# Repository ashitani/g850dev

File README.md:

# g850dev

[ポケコンPC-G850V の開発メモ](https://ashitani.jp/g850/)
のサンプルプログラムやツール類などです。

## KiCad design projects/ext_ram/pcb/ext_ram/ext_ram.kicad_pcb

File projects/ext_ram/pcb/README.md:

# pcb design for pc-g850 memory extension board

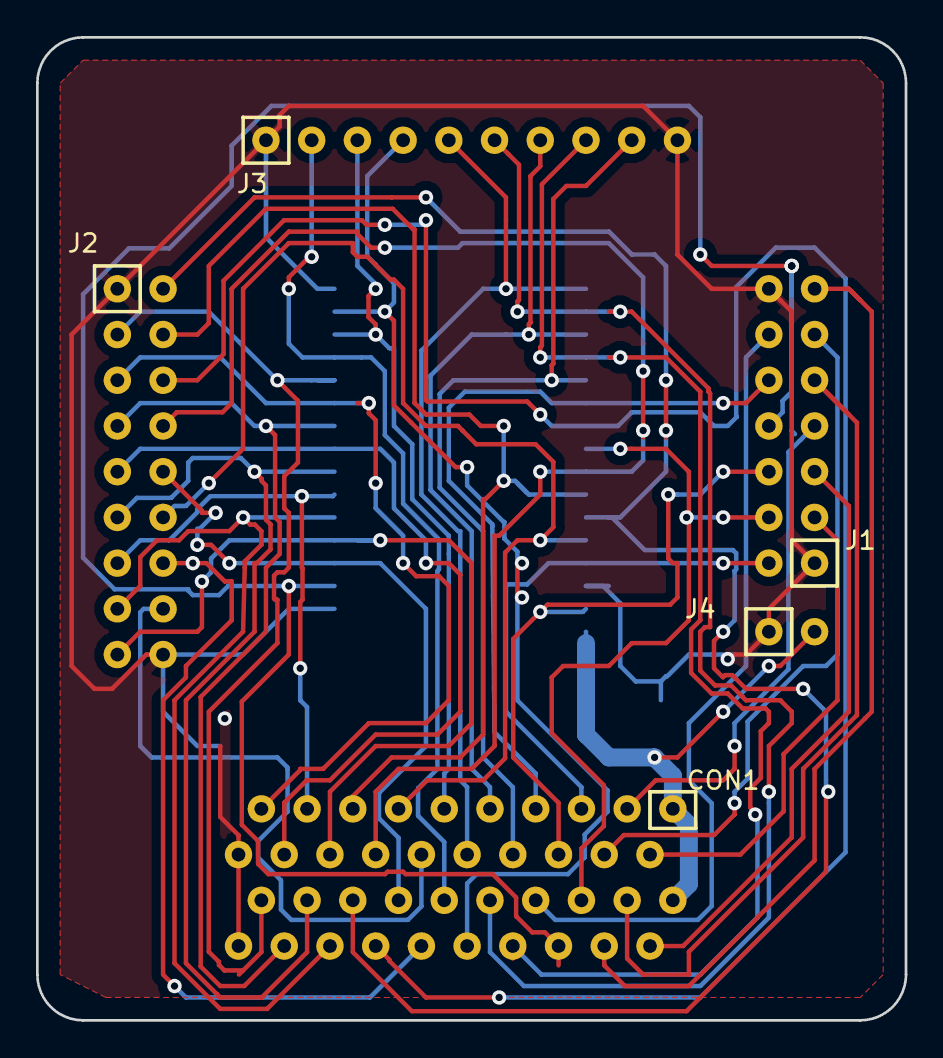
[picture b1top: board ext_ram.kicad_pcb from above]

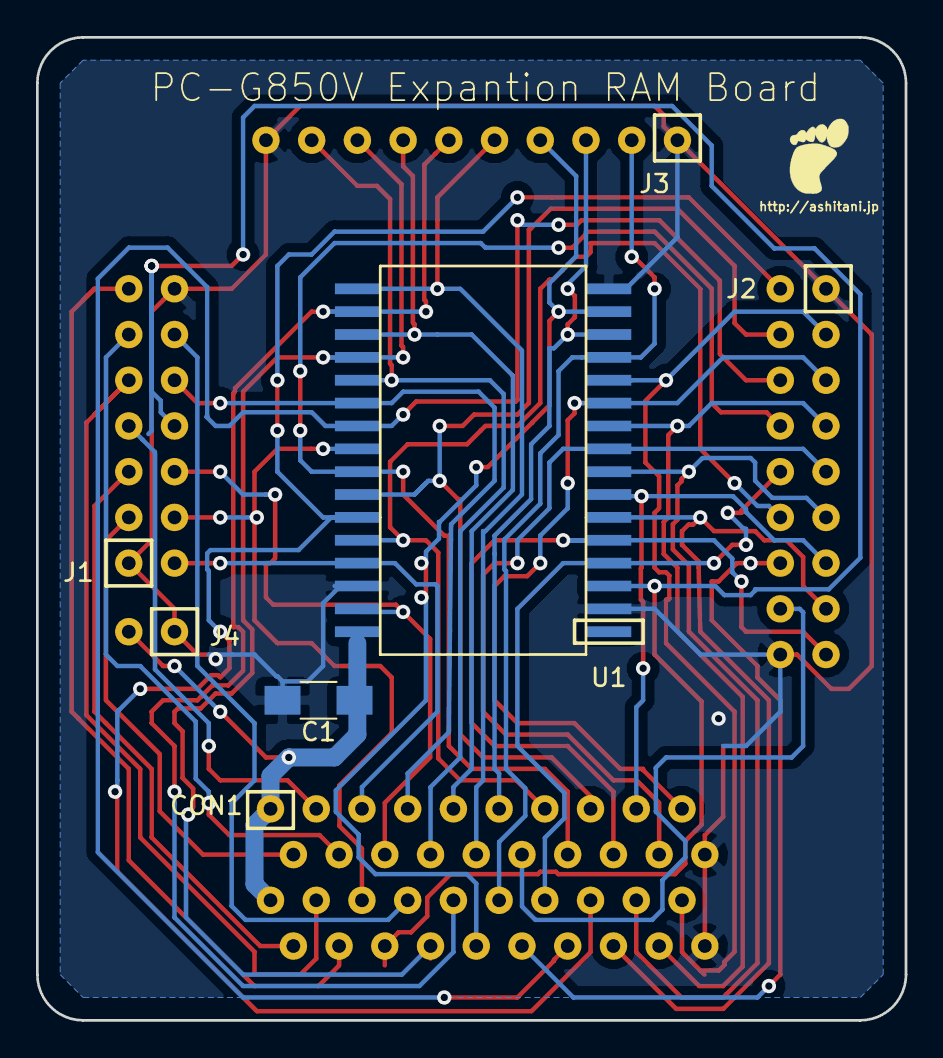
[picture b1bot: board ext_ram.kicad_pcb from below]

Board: 2 copper layers, 48.3 x 54.6 mm, 7 parts (2 on the bottom side), 38 nets.

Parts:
C1: 104; C_1206_HandSoldering
CON1: CARD_BUS
J1: Conn_01x14_Male; CONN_1x14
J2: Conn_01x18_Male; CONN_01x18
J3: Conn_01x10_Male; CONN_1x10
J4: Conn_01x02_Male; CONN_1x2
U1: M68AF127

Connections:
+5V: C1.1, CON1.1, CON1.2, J4.2, U1.32
/A0: CON1.38, J2.2, U1.12
/A1: CON1.37, J2.3, U1.11
/A2: CON1.36, J2.4, U1.10
/A3: CON1.35, J2.5, U1.9
/A4: CON1.34, J2.6, U1.8
/A5: CON1.33, J2.7, U1.7
/A6: CON1.32, J2.8, U1.6
/A7: CON1.31, J2.9, U1.5
/A8: CON1.30, J2.10, U1.27
/A9: CON1.29, J2.11, U1.26
/A10: CON1.28, J2.12, U1.23
/A11: CON1.27, J2.13, U1.25
/A12: CON1.26, J2.14, U1.4
/A13: CON1.25, J2.15, U1.28
/A14: CON1.24, J2.16
/A15: CON1.23, J2.17
/D0: CON1.22, J3.2, U1.13
/D1: CON1.21, J3.3, U1.14
/D2: CON1.20, J3.4, U1.15
/D3: CON1.19, J3.5, U1.17
/D4: CON1.18, J3.6, U1.18
/D5: CON1.17, J3.7, U1.19
/D6: CON1.16, J3.8, U1.20
/D7: CON1.15, J3.9, U1.21
B_A14: CON1.12, J1.11, U1.3
B_A15: CON1.11, J1.10, U1.31
CEROM2: CON1.13, J1.12, U1.22
GND: C1.2, CON1.39, CON1.40, J1.1, J1.14, J2.1, J2.18, J3.1, J3.10, J4.1, U1.2, U1.16, U1.30
unnamed: CON1.3, J1.2
unnamed: CON1.4, J1.3
unnamed: CON1.5, J1.4
unnamed: CON1.6, J1.5
unnamed: CON1.7, J1.6
unnamed: CON1.8, J1.7
unnamed: CON1.14, J1.13
RD_: CON1.10, J1.9, U1.24
WR_: CON1.9, J1.8, U1.29

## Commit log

2018-12-28 added bsave/decode.py
2018-12-28 added bload
2018-12-28 modified readme
2021-05-01 add xsm examples
